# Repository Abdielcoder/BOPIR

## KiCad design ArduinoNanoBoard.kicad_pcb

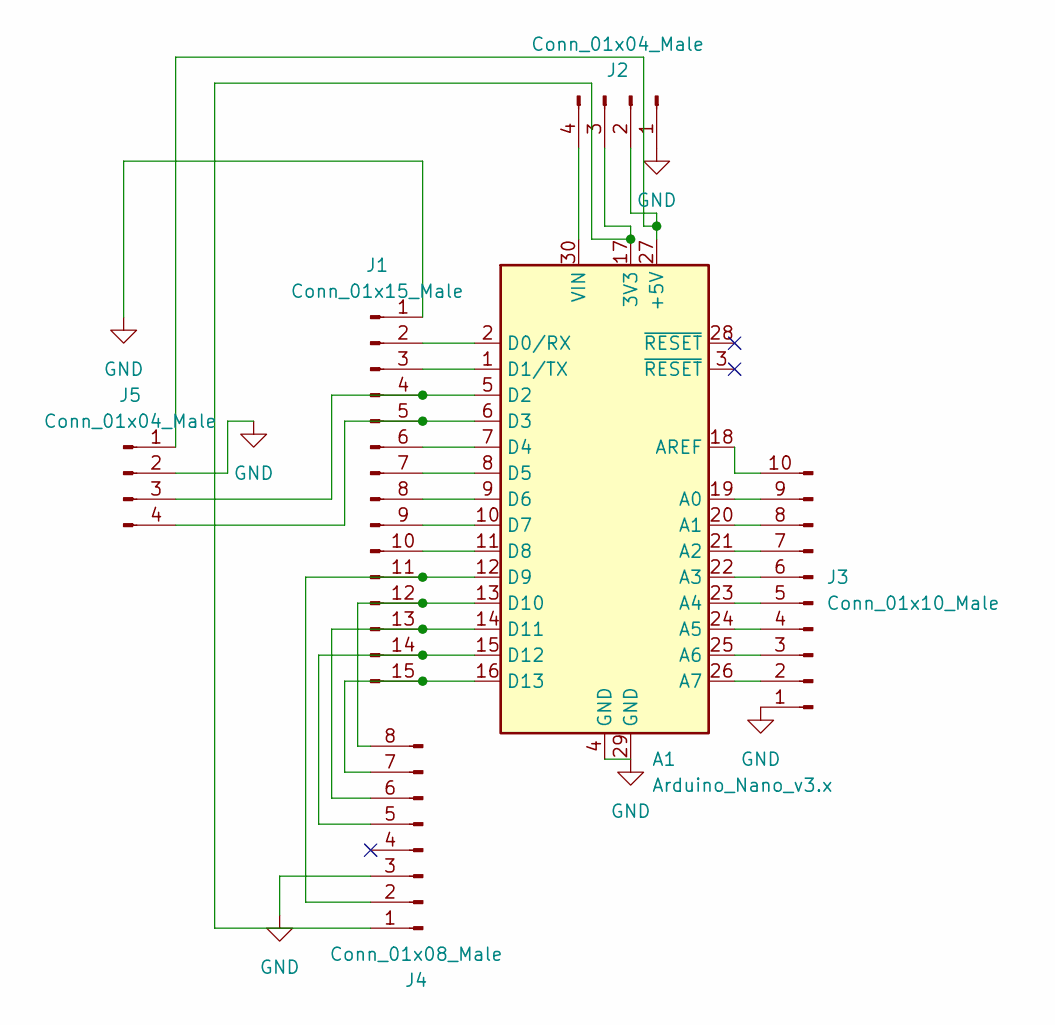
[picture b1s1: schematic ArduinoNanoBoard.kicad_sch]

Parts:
A1: Arduino_Nano_v3.x; Arduino_Nano
J1: Conn_01x15_Male; PinHeader_1x15_P2.54mm_Vertical
J2, J5: Conn_01x04_Male; PinHeader_1x04_P2.54mm_Vertical
J3: Conn_01x10_Male; PinHeader_1x10_P2.54mm_Vertical
J4: Conn_01x08_Male; PinHeader_1x08_P2.54mm_Vertical

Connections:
GND: A1.4 (GND), A1.29 (GND), J1.1, J2.1, J3.1, J4.3, J5.2
unnamed: A1.1 (D1/TX), J1.3
unnamed: A1.2 (D0/RX), J1.2
unnamed: A1.5 (D2), J1.4, J5.3
unnamed: A1.6 (D3), J1.5, J5.4
unnamed: A1.7 (D4), J1.6
unnamed: A1.8 (D5), J1.7
unnamed: A1.9 (D6), J1.8
unnamed: A1.10 (D7), J1.9
unnamed: A1.11 (D8), J1.10
unnamed: A1.12 (D9), J1.11, J4.2
unnamed: A1.13 (D10), J1.12, J4.8
unnamed: A1.14 (D11), J1.13, J4.6
unnamed: A1.15 (D12), J1.14, J4.5
unnamed: A1.16 (D13), J1.15, J4.7
unnamed: A1.17 (3V3), J2.3, J4.1
unnamed: A1.18 (AREF), J3.10
unnamed: A1.19 (A0), J3.9
unnamed: A1.20 (A1), J3.8
unnamed: A1.21 (A2), J3.7
unnamed: A1.22 (A3), J3.6
unnamed: A1.23 (A4), J3.5
unnamed: A1.24 (A5), J3.4
unnamed: A1.25 (A6), J3.3
unnamed: A1.26 (A7), J3.2
unnamed: A1.27 (+5V), J2.2, J5.1
unnamed: A1.30 (VIN), J2.4

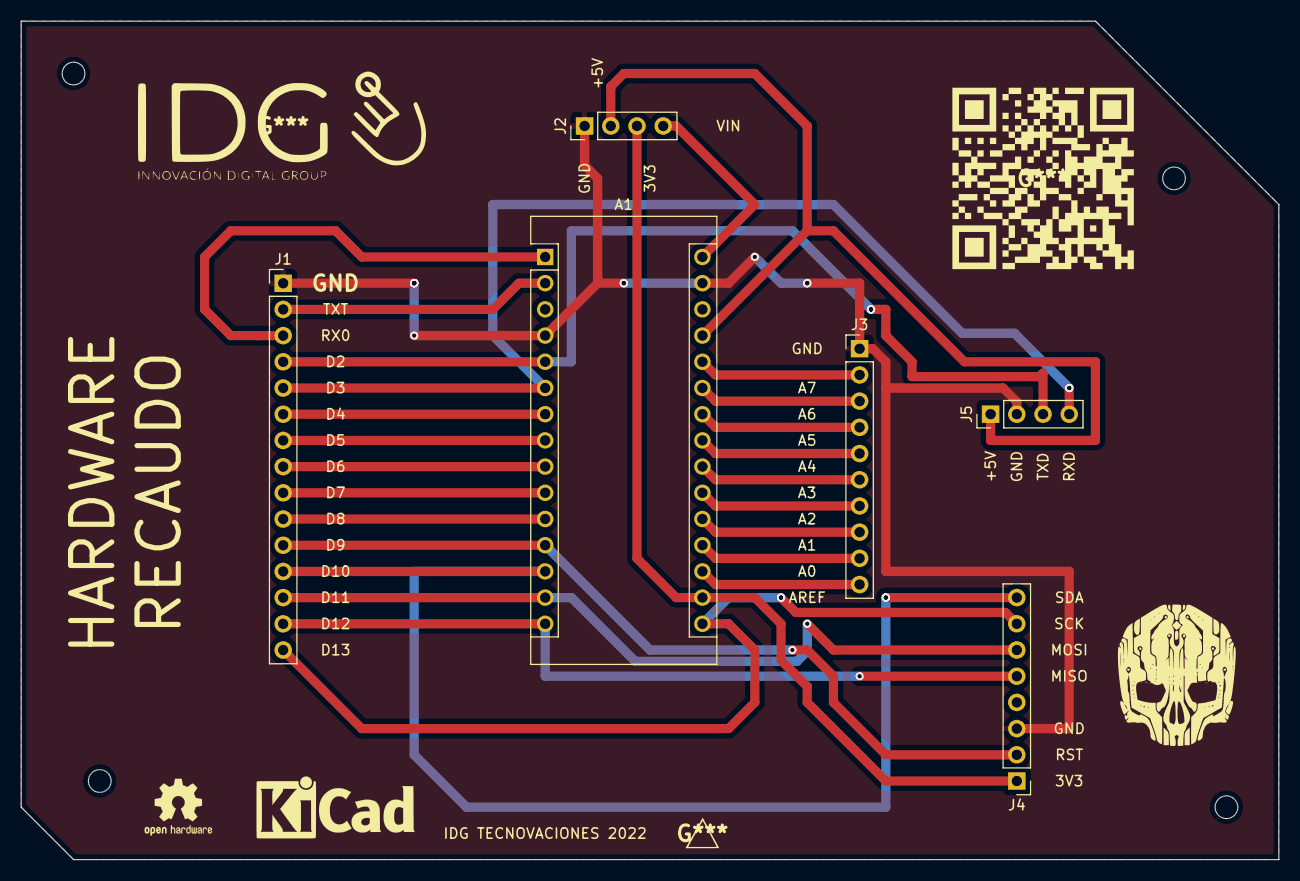
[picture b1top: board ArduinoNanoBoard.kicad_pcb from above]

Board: 2 copper layers, 121.9 x 81.3 mm, 6 parts (0 on the bottom side), 27 nets.

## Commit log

2022-01-14 BORPI01 - NANO BOARD AND VIAS
2022-01-14 BOPIR02 ADD FINGERPRINTS
2022-01-14 BOPIR03 - J CONECTORS RFID AND BLUETOOTH
2022-01-15 BOPIR04 - ADDING BORDING LINE TO CUT
2022-01-16 BOPIR05 - ADD HOLES TO PCB
